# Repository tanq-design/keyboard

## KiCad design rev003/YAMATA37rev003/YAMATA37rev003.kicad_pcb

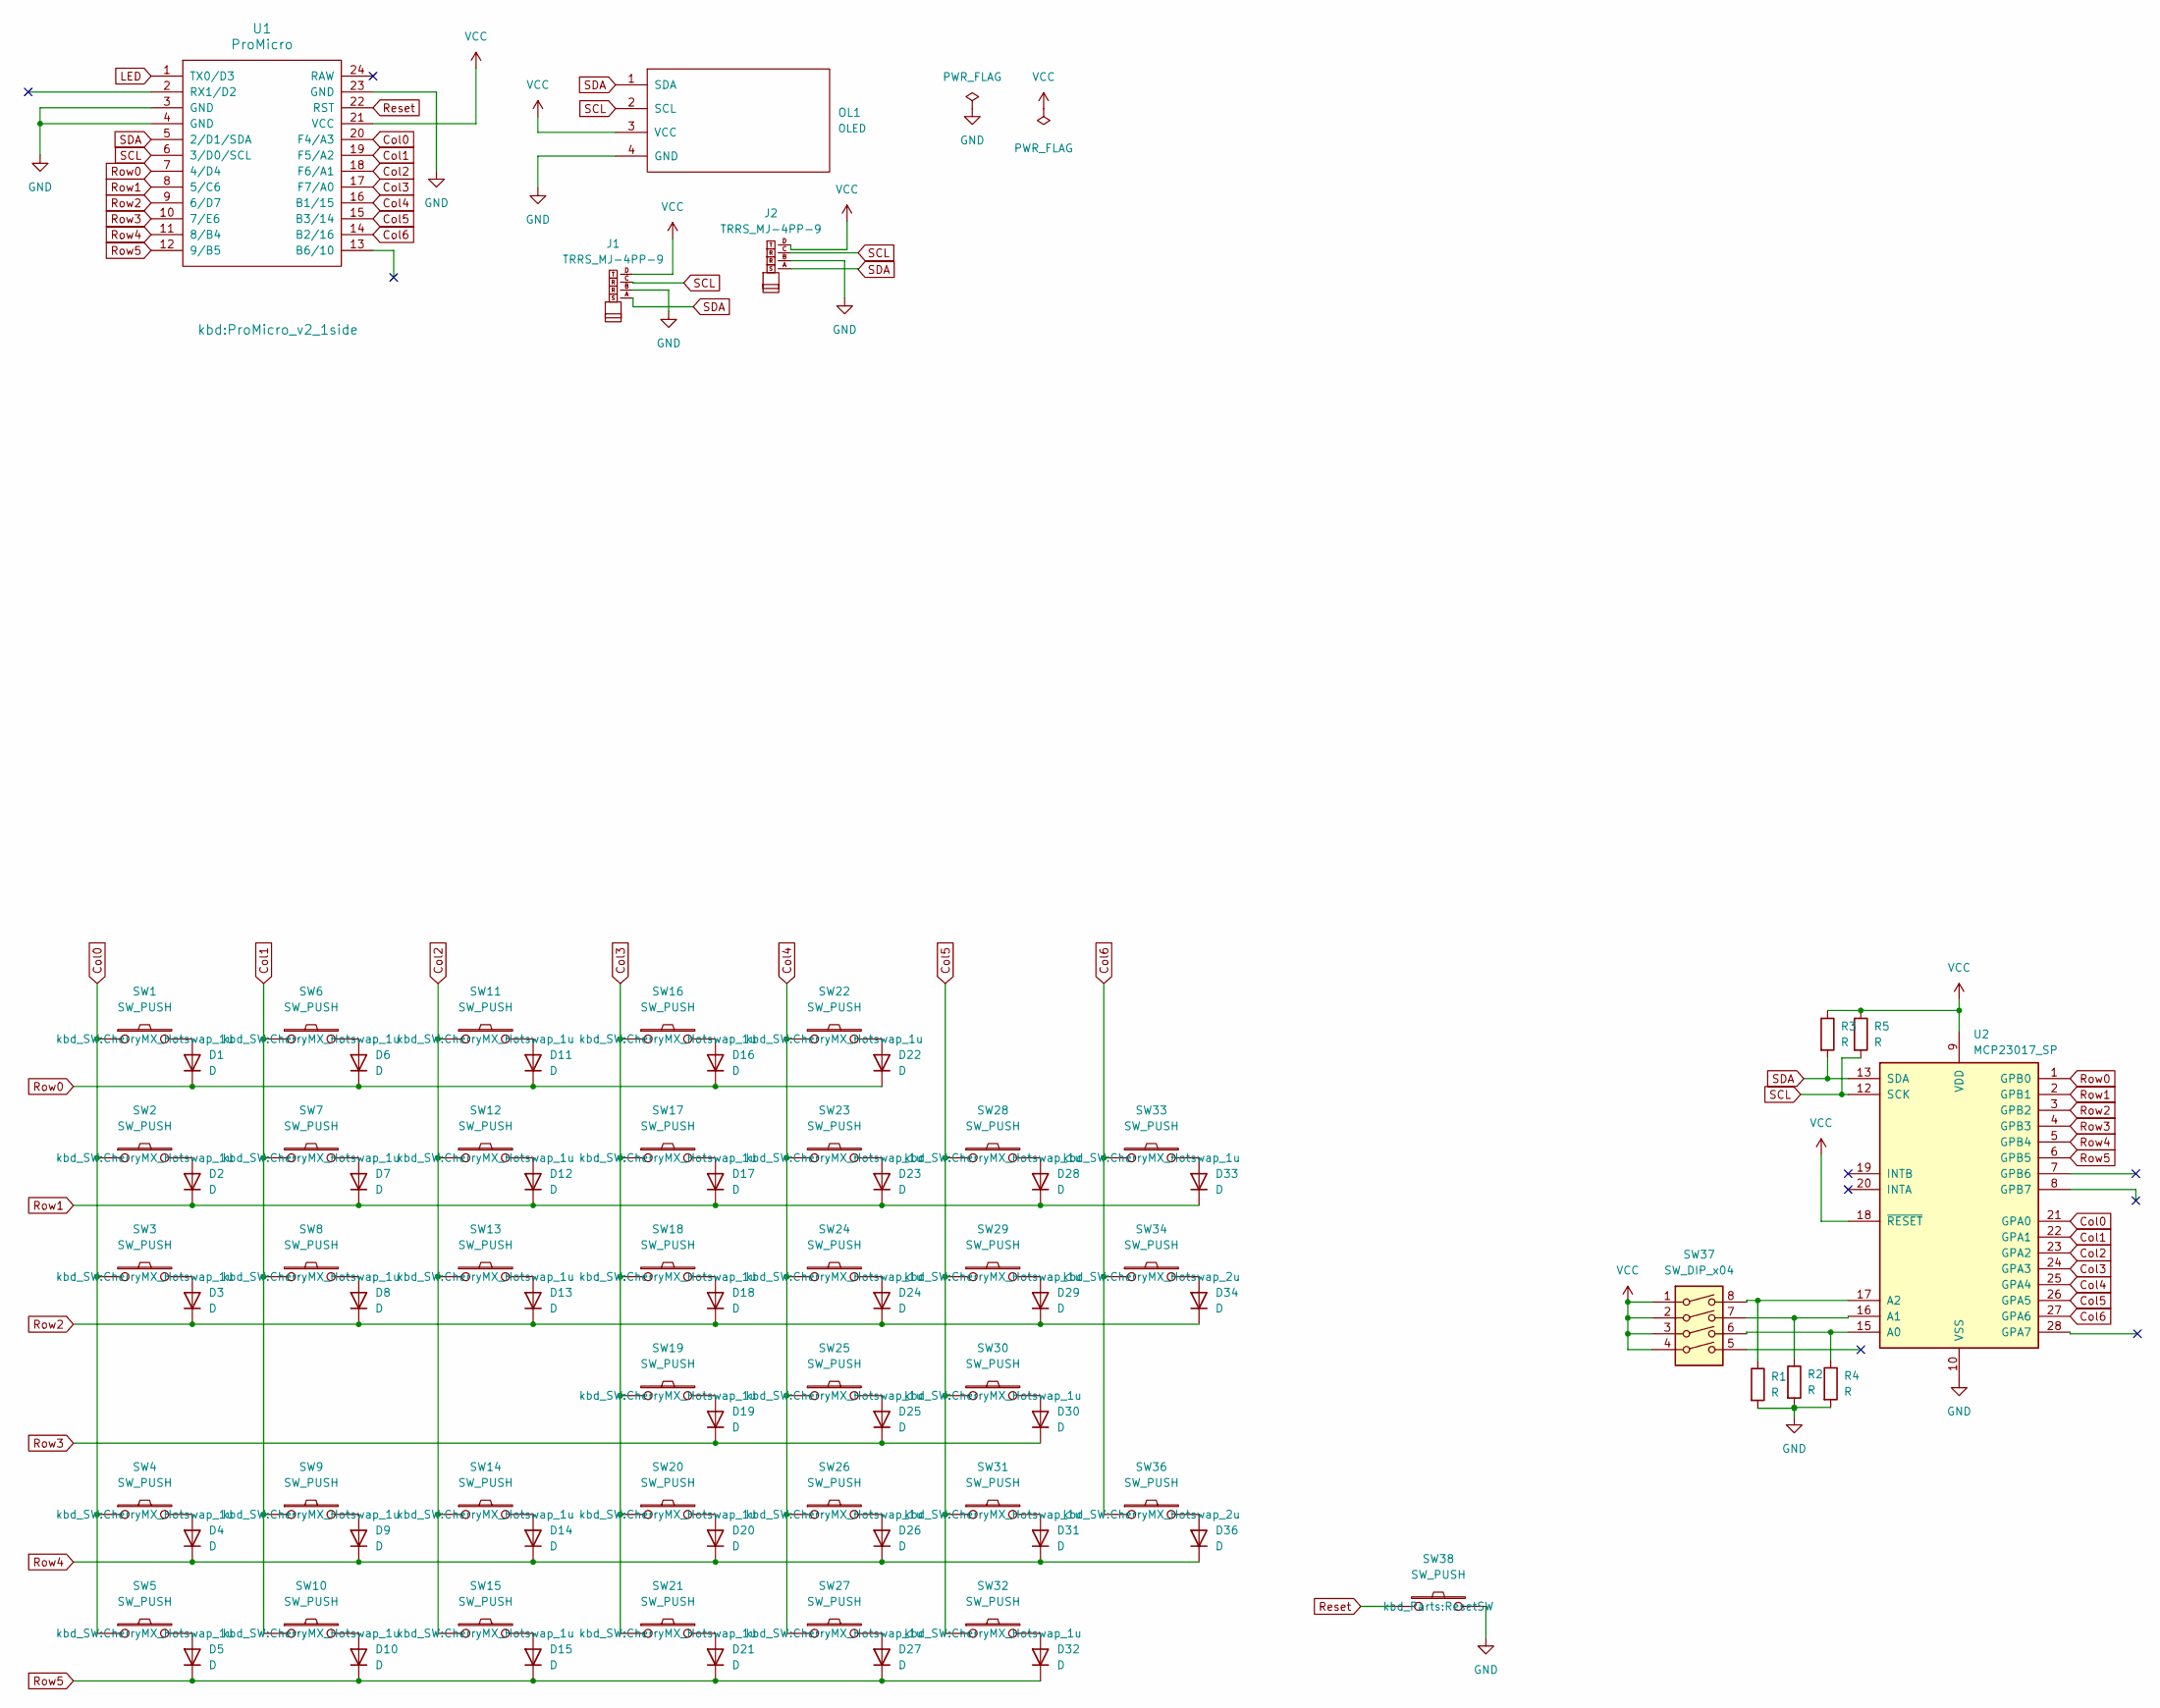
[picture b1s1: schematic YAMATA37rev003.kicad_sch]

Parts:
D1, D2, D3, D4, D5, D6, D7, D8, D9, D10, D11, D12, D13, D14, D15, D16, D17, D18, D19, D20, D21, D22, D23, D24, D25, D26, D27, D28, D29, D30, D31, D32, D33, D34, D36: D; Diode_TH_SMD
J1, J2: TRRS_MJ-4PP-9
OL1: OLED
R1, R2, R3, R4, R5: R; R_Axial_DIN0207_L6.3mm_D2.5mm_P7.62mm_Horizontal
SW1, SW2, SW3, SW4, SW5, SW6, SW7, SW8, SW9, SW10, SW11, SW12, SW13, SW14, SW15, SW16, SW17, SW18, SW19, SW20, SW21, SW22, SW23, SW24, SW25, SW26, SW27, SW28, SW29, SW30, SW31, SW32, SW33: SW_PUSH; CherryMX_Hotswap_1u
SW34, SW36: SW_PUSH; CherryMX_Hotswap_2u
SW37: SW_DIP_x04; DIP-8_W10.16mm
SW38: SW_PUSH; ResetSW
U1: ProMicro; ProMicro_v2_1side
U2: MCP23017_SP; DIP-28_W7.62mm

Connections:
Col0: SW1.1, SW2.1, SW3.1, SW4.1, SW5.1, U1.20 (F4/A3), U2.21 (GPA0)
Col1: SW6.1, SW7.1, SW8.1, SW9.1, SW10.1, U1.19 (F5/A2), U2.22 (GPA1)
Col2: SW11.1, SW12.1, SW13.1, SW14.1, SW15.1, U1.18 (F6/A1), U2.23 (GPA2)
Col3: SW16.1, SW17.1, SW18.1, SW19.1, SW20.1, SW21.1, U1.17 (F7/A0), U2.24 (GPA3)
Col4: SW22.1, SW23.1, SW24.1, SW25.1, SW26.1, SW27.1, U1.16 (B1/15), U2.25 (GPA4)
Col5: SW28.1, SW29.1, SW30.1, SW31.1, SW32.1, U1.15 (B3/14), U2.26 (GPA5)
LED: U1.1 (TX0/D3)
unnamed: D1.2 (A), SW1.2
unnamed: D2.2 (A), SW2.2
unnamed: D3.2 (A), SW3.2
unnamed: D4.2 (A), SW4.2
unnamed: D5.2 (A), SW5.2
unnamed: D6.2 (A), SW6.2
unnamed: D7.2 (A), SW7.2
unnamed: D8.2 (A), SW8.2
unnamed: D9.2 (A), SW9.2
unnamed: D10.2 (A), SW10.2
unnamed: D11.2 (A), SW11.2
unnamed: D12.2 (A), SW12.2
unnamed: D13.2 (A), SW13.2
unnamed: D14.2 (A), SW14.2
unnamed: D15.2 (A), SW15.2
unnamed: D16.2 (A), SW16.2
unnamed: D17.2 (A), SW17.2
unnamed: D18.2 (A), SW18.2
unnamed: D19.2 (A), SW19.2
unnamed: D20.2 (A), SW20.2
unnamed: D21.2 (A), SW21.2
unnamed: D22.2 (A), SW22.2
unnamed: D23.2 (A), SW23.2
unnamed: D24.2 (A), SW24.2
unnamed: D25.2 (A), SW25.2
unnamed: D26.2 (A), SW26.2
unnamed: D27.2 (A), SW27.2
unnamed: D28.2 (A), SW28.2
unnamed: D29.2 (A), SW29.2
unnamed: D30.2 (A), SW30.2
unnamed: D31.2 (A), SW31.2
unnamed: D32.2 (A), SW32.2
unnamed: D33.2 (A), SW33.2
unnamed: D34.2 (A), SW34.2
unnamed: R4.1, SW37.6, U2.15 (A0)
unnamed: R2.1, SW37.7, U2.16 (A1)
unnamed: R1.1, SW37.8, U2.17 (A2)
Row0: D1.1 (K), D6.1 (K), D11.1 (K), D16.1 (K), D22.1 (K), U1.7 (4/D4), U2.1 (GPB0)
Row1: D2.1 (K), D7.1 (K), D12.1 (K), D17.1 (K), D23.1 (K), D28.1 (K), D33.1 (K), U1.8 (5/C6), U2.2 (GPB1)
Row2: D3.1 (K), D8.1 (K), D13.1 (K), D18.1 (K), D24.1 (K), D29.1 (K), D34.1 (K), U1.9 (6/D7), U2.3 (GPB2)
Row3: D19.1 (K), D25.1 (K), D30.1 (K), U1.10 (7/E6), U2.4 (GPB3)
Row4: D4.1 (K), D9.1 (K), D14.1 (K), D20.1 (K), D26.1 (K), D31.1 (K), U1.11 (8/B4), U2.5 (GPB4); also elsewhere on the board
Row5: D5.1 (K), D10.1 (K), D15.1 (K), D21.1 (K), D27.1 (K), D32.1 (K), U1.12 (9/B5), U2.6 (GPB5)
SCL: J1.C, J2.C, OL1.2 (SCL), R5.2, U1.6 (3/D0/SCL), U2.12 (SCK)
SDA: J1.A, J2.A, OL1.1 (SDA), R3.2, U1.5 (2/D1/SDA), U2.13 (SDA)
VCC: J1.D, J2.D, OL1.3 (VCC), R3.1, R5.1, SW37.1, SW37.2, SW37.3, SW37.4, U1.21 (VCC), U2.9 (VDD), U2.18 (~RESET)

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
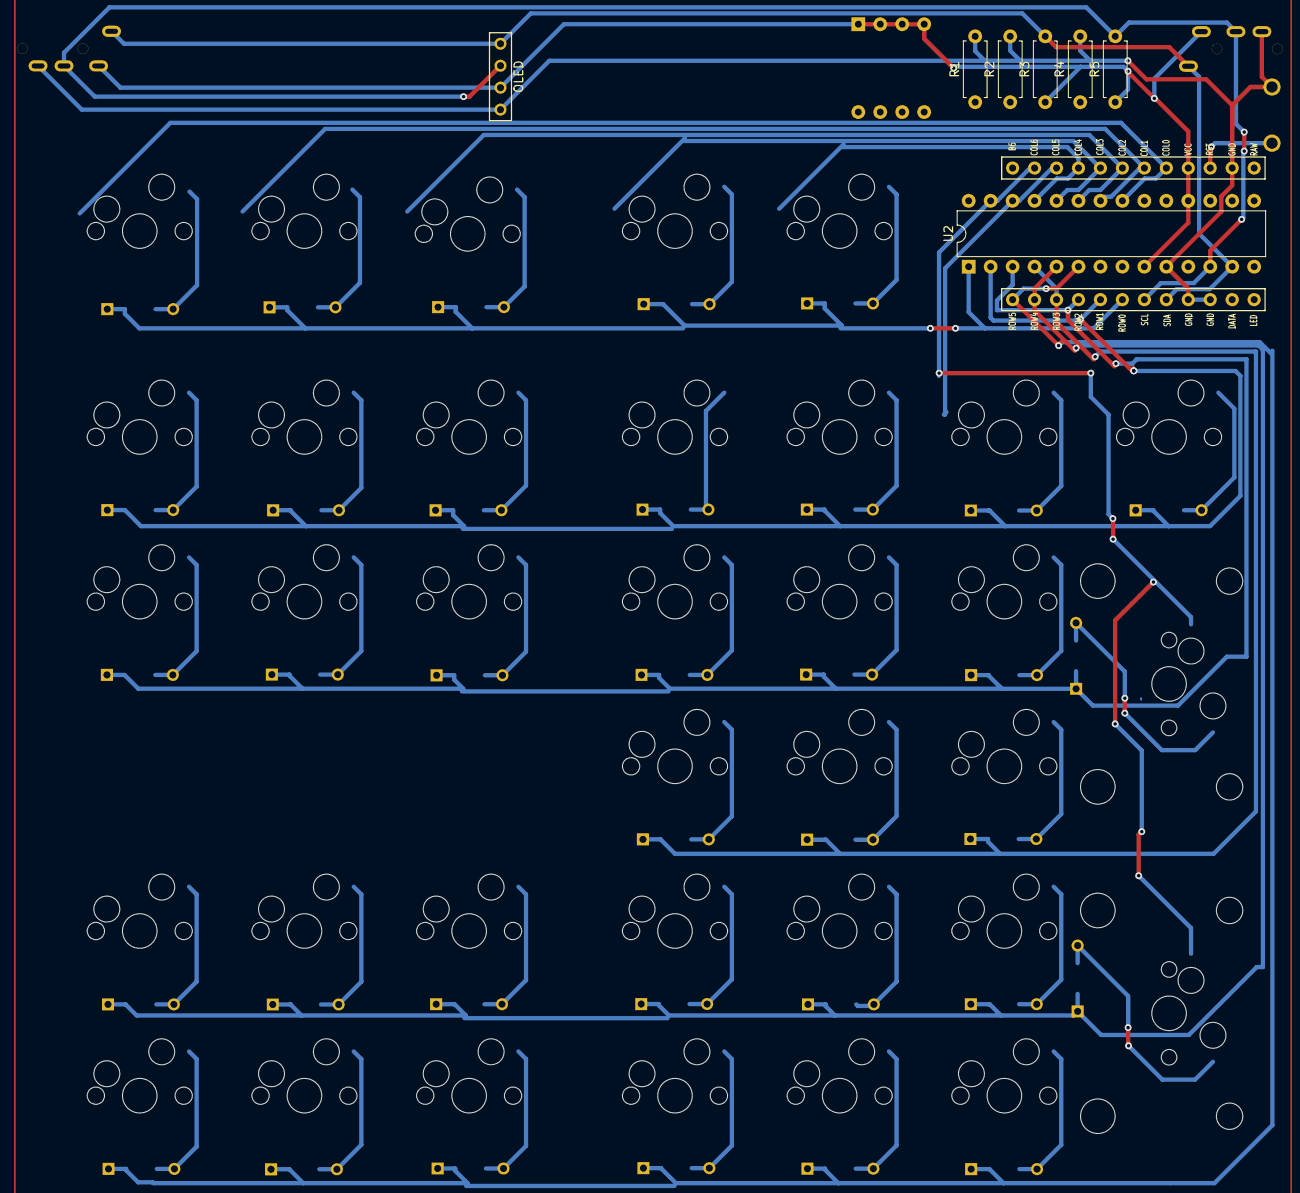
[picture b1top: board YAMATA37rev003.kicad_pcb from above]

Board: 2 copper layers, 82 parts (1 on the bottom side), 56 nets.

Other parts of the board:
D35: D; Diode_TH_SMD
SW35: SW_PUSH; CherryMX_Hotswap_2u

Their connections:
Row4: D35.1 (K); also elsewhere on the board

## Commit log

2023-08-09 Yamata37 rev.0.0.2
2023-08-15 rev002
2023-08-16 gitignore
2023-09-26 liteWasd
